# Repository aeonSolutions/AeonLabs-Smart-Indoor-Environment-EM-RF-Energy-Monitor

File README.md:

[ ](https://discord.gg/hw3j3RwfJf)

[PCB-Prototyping-Catalogue](https://github.com/aeonSolutions/PCB-Prototyping-Catalogue)  >>   [Home-Automation](https://github.com/aeonSolutions/PCB-Prototyping-Catalogue/tree/main/Home-Automation)  >>  [Safety & Health](https://github.com/aeonSolutions/AeonLabs-Safety-Health)   >>  >>  Smart Indoor Environment EM RF Energy Monitor

<br>

⚠️ **Start by reading the documentation first**. [Click here to open it](https://github.com/aeonSolutions/AeonLabs-Safety-Health/wiki) 

# Smart Indoor Environment EM RF Energy Monitor

**The Problem**

Nowadays there are a plethora of electronic devices with wireless electromagnetic (EM) capabilities. So much, is possible, for one living in a building apartment to query nearby neighboring devices. Such superposition of EM frequencies increases the risk of random (or not) energy spikes within any indoor spaces where the different devices' wireless signals exist simultaneously. The most common danger to the health of a person is found in the literature by "electromagnetic burns". Although such energy spike events are not common, when devices are setup and even programmed to broadcast in such a way are always dangerous to one's health.  

**The Idea**

This Smart Indoor Environment EM RF Energy Monitor does not solve the electromagnetic health concern one may have indoors. However, is a step forward in correctly identifying such electromagnetic disturbances nearby, for instance, when observing recurrently a mid-air energy spike, with the most common visual effect, a really small bright light flash. This smart device is able to do electromagnetic (EM) radio frequency (RF) measurements in a room and send data measurements to a local home server, alternatively to a public cloud server, for instance, to the authorities on a data repository ( see http://wwww.dataverse.org). Another important characteristic of this smart device is in the ability to deliver data to a server with a Unique Data Fingerprint Identification (UDF-ID),  which makes collected data more trustworthy of its origins.

<br>

### Status

 Not yet tested.

<br>

### Circuit Schematic 

<br>
  
### Known PCB bugs
This public revision of the PCB electronics has a few unknown errors. 

<br>

<br>
  
  ## Compatibility

<p align="center">

</p>

<br>

## What one additionally needs
- [USB to UART/USB TTL firmware burner for 5V and 3.3V MCUs ](https://github.com/aeonSolutions/PCB-Prototyping-Catalogue/blob/main/DIY-Maker/README.md) 
<br />
<br />

**Get a Notification on every PCB update**

|  | You can fill in your [email here (Google form)](https://docs.google.com/forms/d/e/1FAIpQLScErMgQYRdA-umvCjvTPPrCO7Lg1QYowTxb7vfa8cTfrcPEAA/viewform?usp=pp_url) and I'll send a reminder when a new PCB prototype is made available here or a new revision for an existing PCB. Stay tuned! |
|-------------|------|

<br />

## Buy the PRO version on Tindie

|  | To all those not into electronics and still liked and want to own any of the listed PCB for smart devices can buy the PRO version on Tindie ready to install and use. |
|-------------|------|

### Useful links 
Below is a list of links with useful information about these kinds of abusive and many times criminal and terrorist usages.
[continue reading ...](https://github.com/aeonSolutions/AeonLabs-Safety-Health/wiki/Useful-Links)

<br />
<br />

**Get a Notification on every PCB update**

|  | You can fill in your [email here (Google form)](https://docs.google.com/forms/d/e/1FAIpQLScErMgQYRdA-umvCjvTPPrCO7Lg1QYowTxb7vfa8cTfrcPEAA/viewform?usp=pp_url) and I'll send a reminder when a new PCB prototype is made available here or a new revision for an existing PCB. Stay tuned! |
|-------------|------|

<br>

**Hire AeonLabs** <br>
If you like my work here and are looking to design and deploy your own smart device find [here](https://github.com/aeonSolutions/PCB-Prototyping-Catalogue/wiki/How-to-Hire-AeonLabs) how to hire me. 

<br>

## Author

You can get in touch with me on my LinkedIn Profile:

#### Miguel Tomas

You can also follow my GitHub Profile to stay updated about my latest projects: 

<br>

### Be supportive of my dedication and work towards technology education and buy me a cup of coffee
The PCB Design Files I provide here for anyone to use are free. If you like this Smart Device or use it, please consider buying me a cup of coffee, a slice of pizza, or a book to help me study, eat, and think new PCB design files.

<br />

### Make a donation on Paypal
Make a donation on PayPal and get a TAX refund*.

### License

Before proceeding to download any of AeonLabs open source code for software solutions and/or open hardware electronics for smart devices and data acquisition make sure you are choosing the right license for your project. See [AeonLabs Solutions for Open Hardware & Open Source Code](https://github.com/aeonSolutions/PCB-Prototyping-Catalogue/wiki/AeonLabs-Solutions-for-Open-Hardware-&-Source-Development) for more information. For commercial business solutions contact AeonLabs for more information ℹ️ using the contacts above. Thank you 🙏.

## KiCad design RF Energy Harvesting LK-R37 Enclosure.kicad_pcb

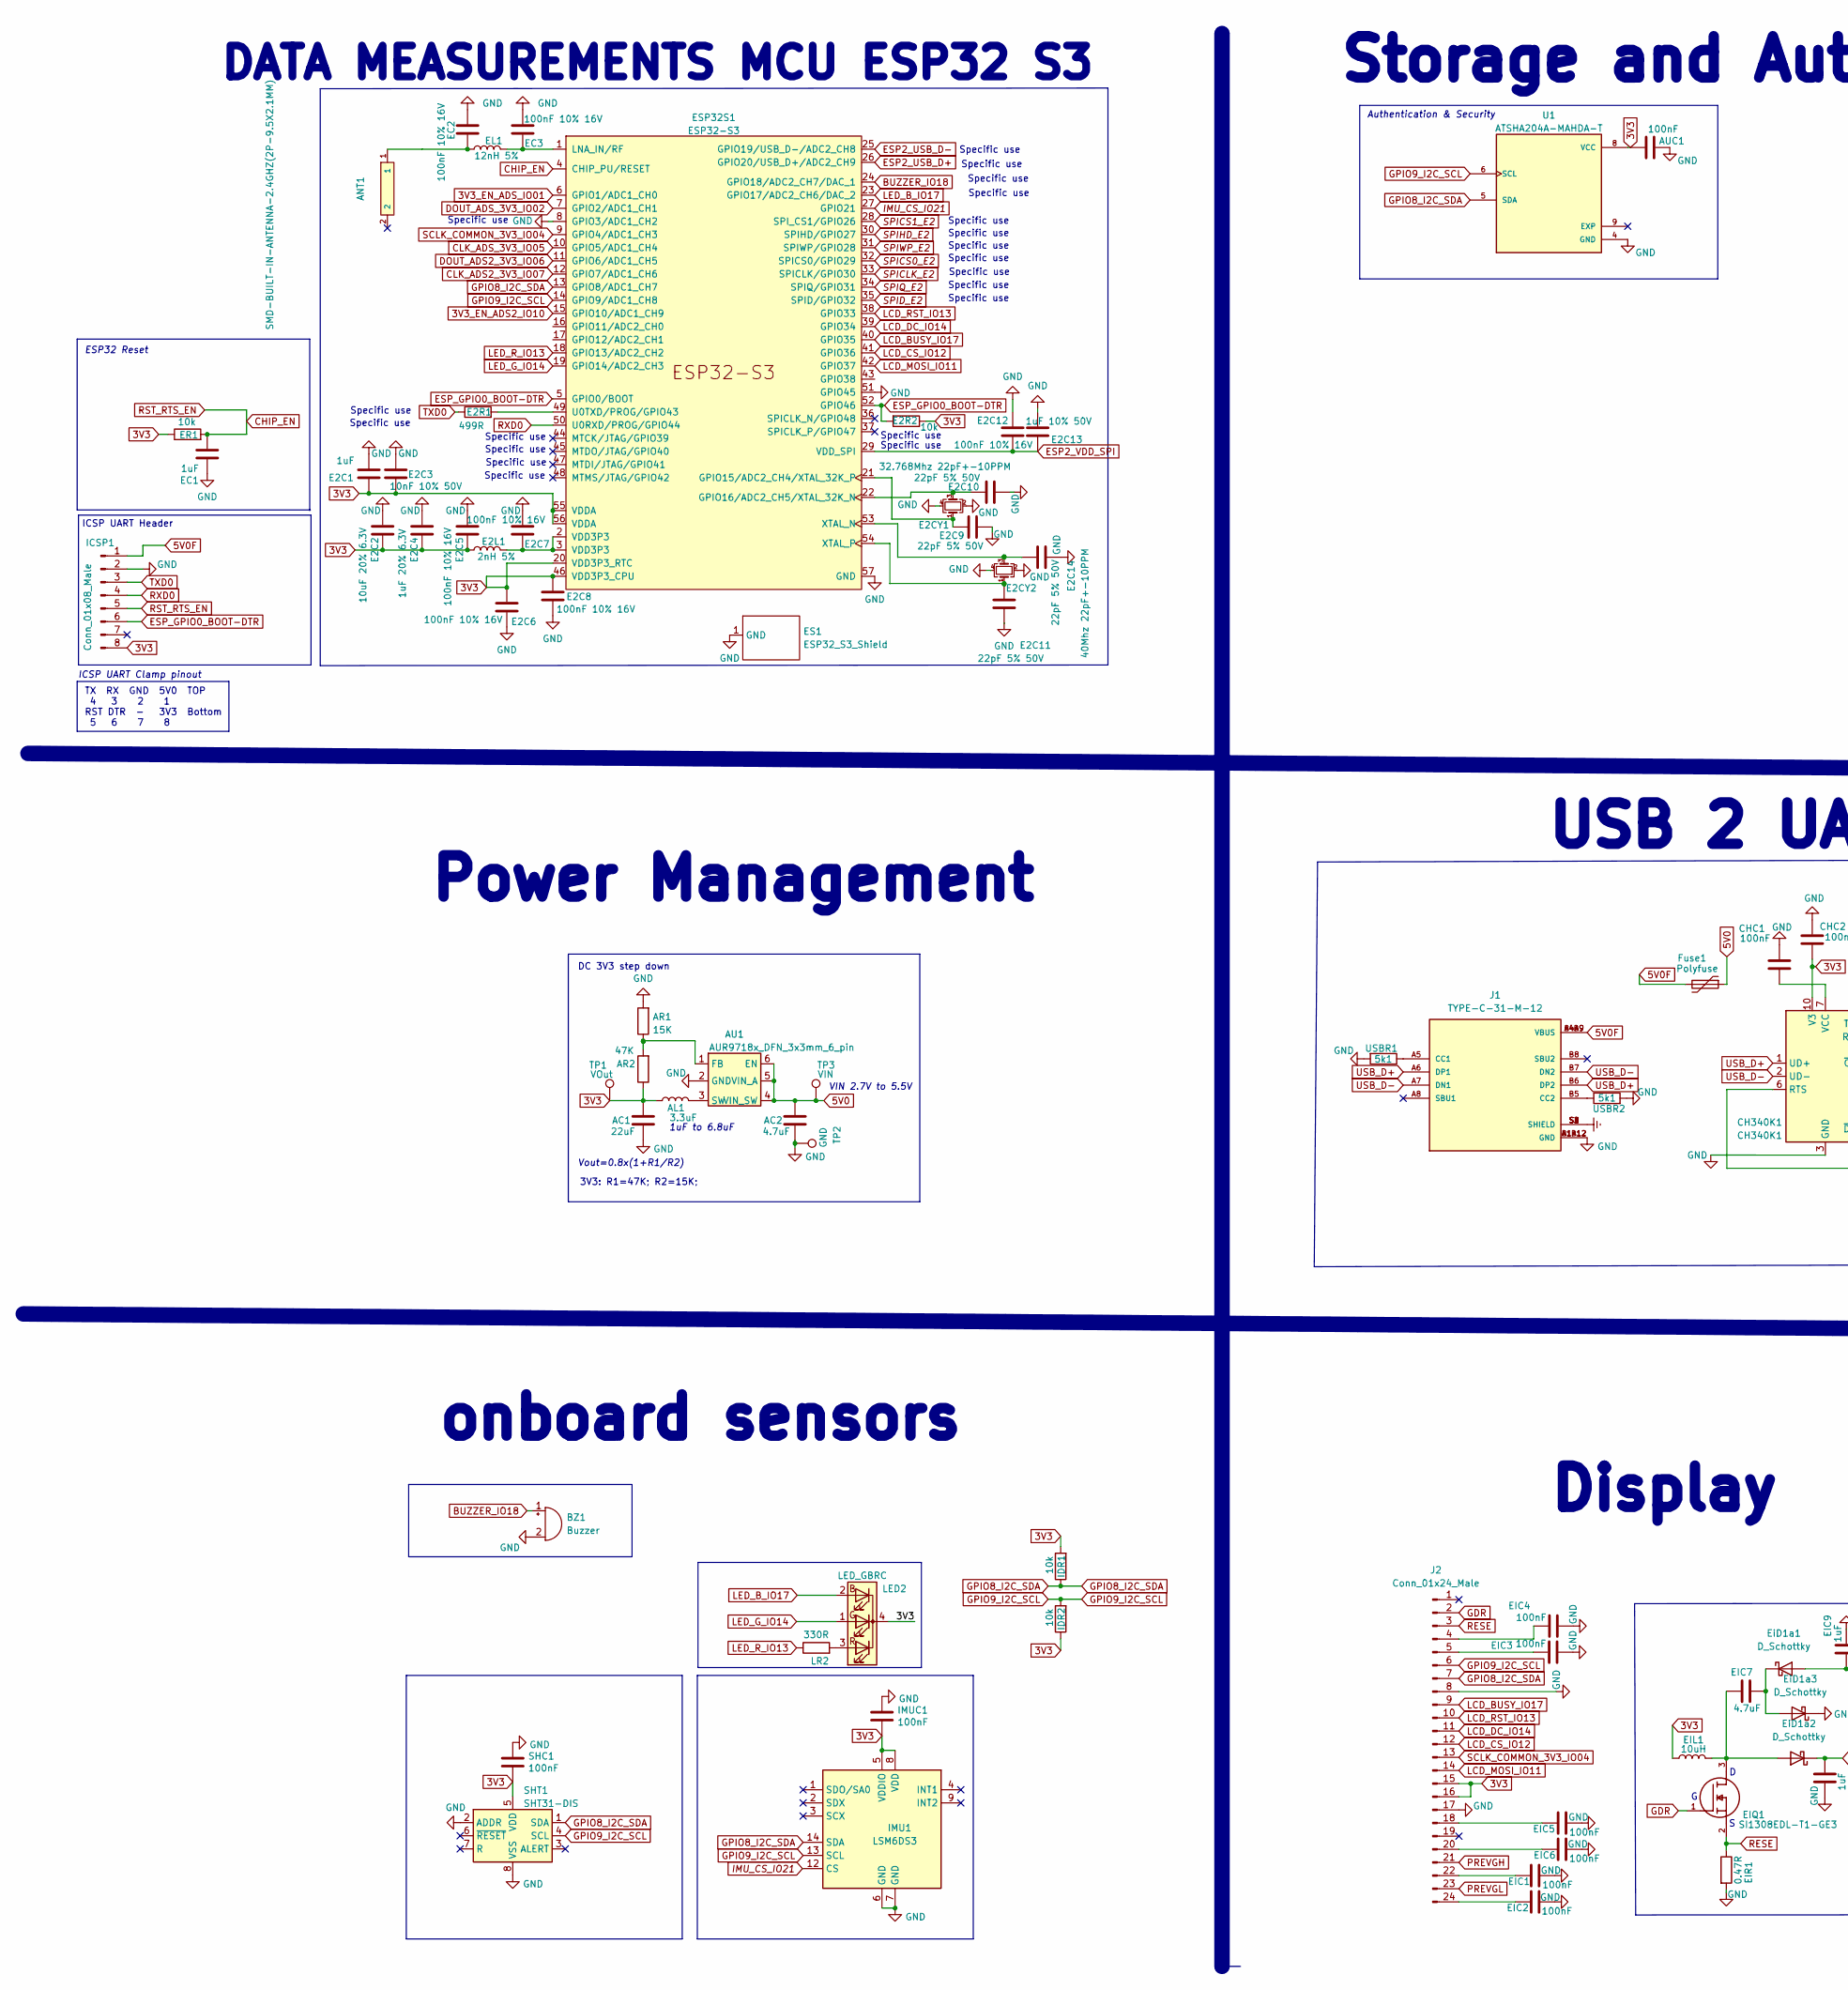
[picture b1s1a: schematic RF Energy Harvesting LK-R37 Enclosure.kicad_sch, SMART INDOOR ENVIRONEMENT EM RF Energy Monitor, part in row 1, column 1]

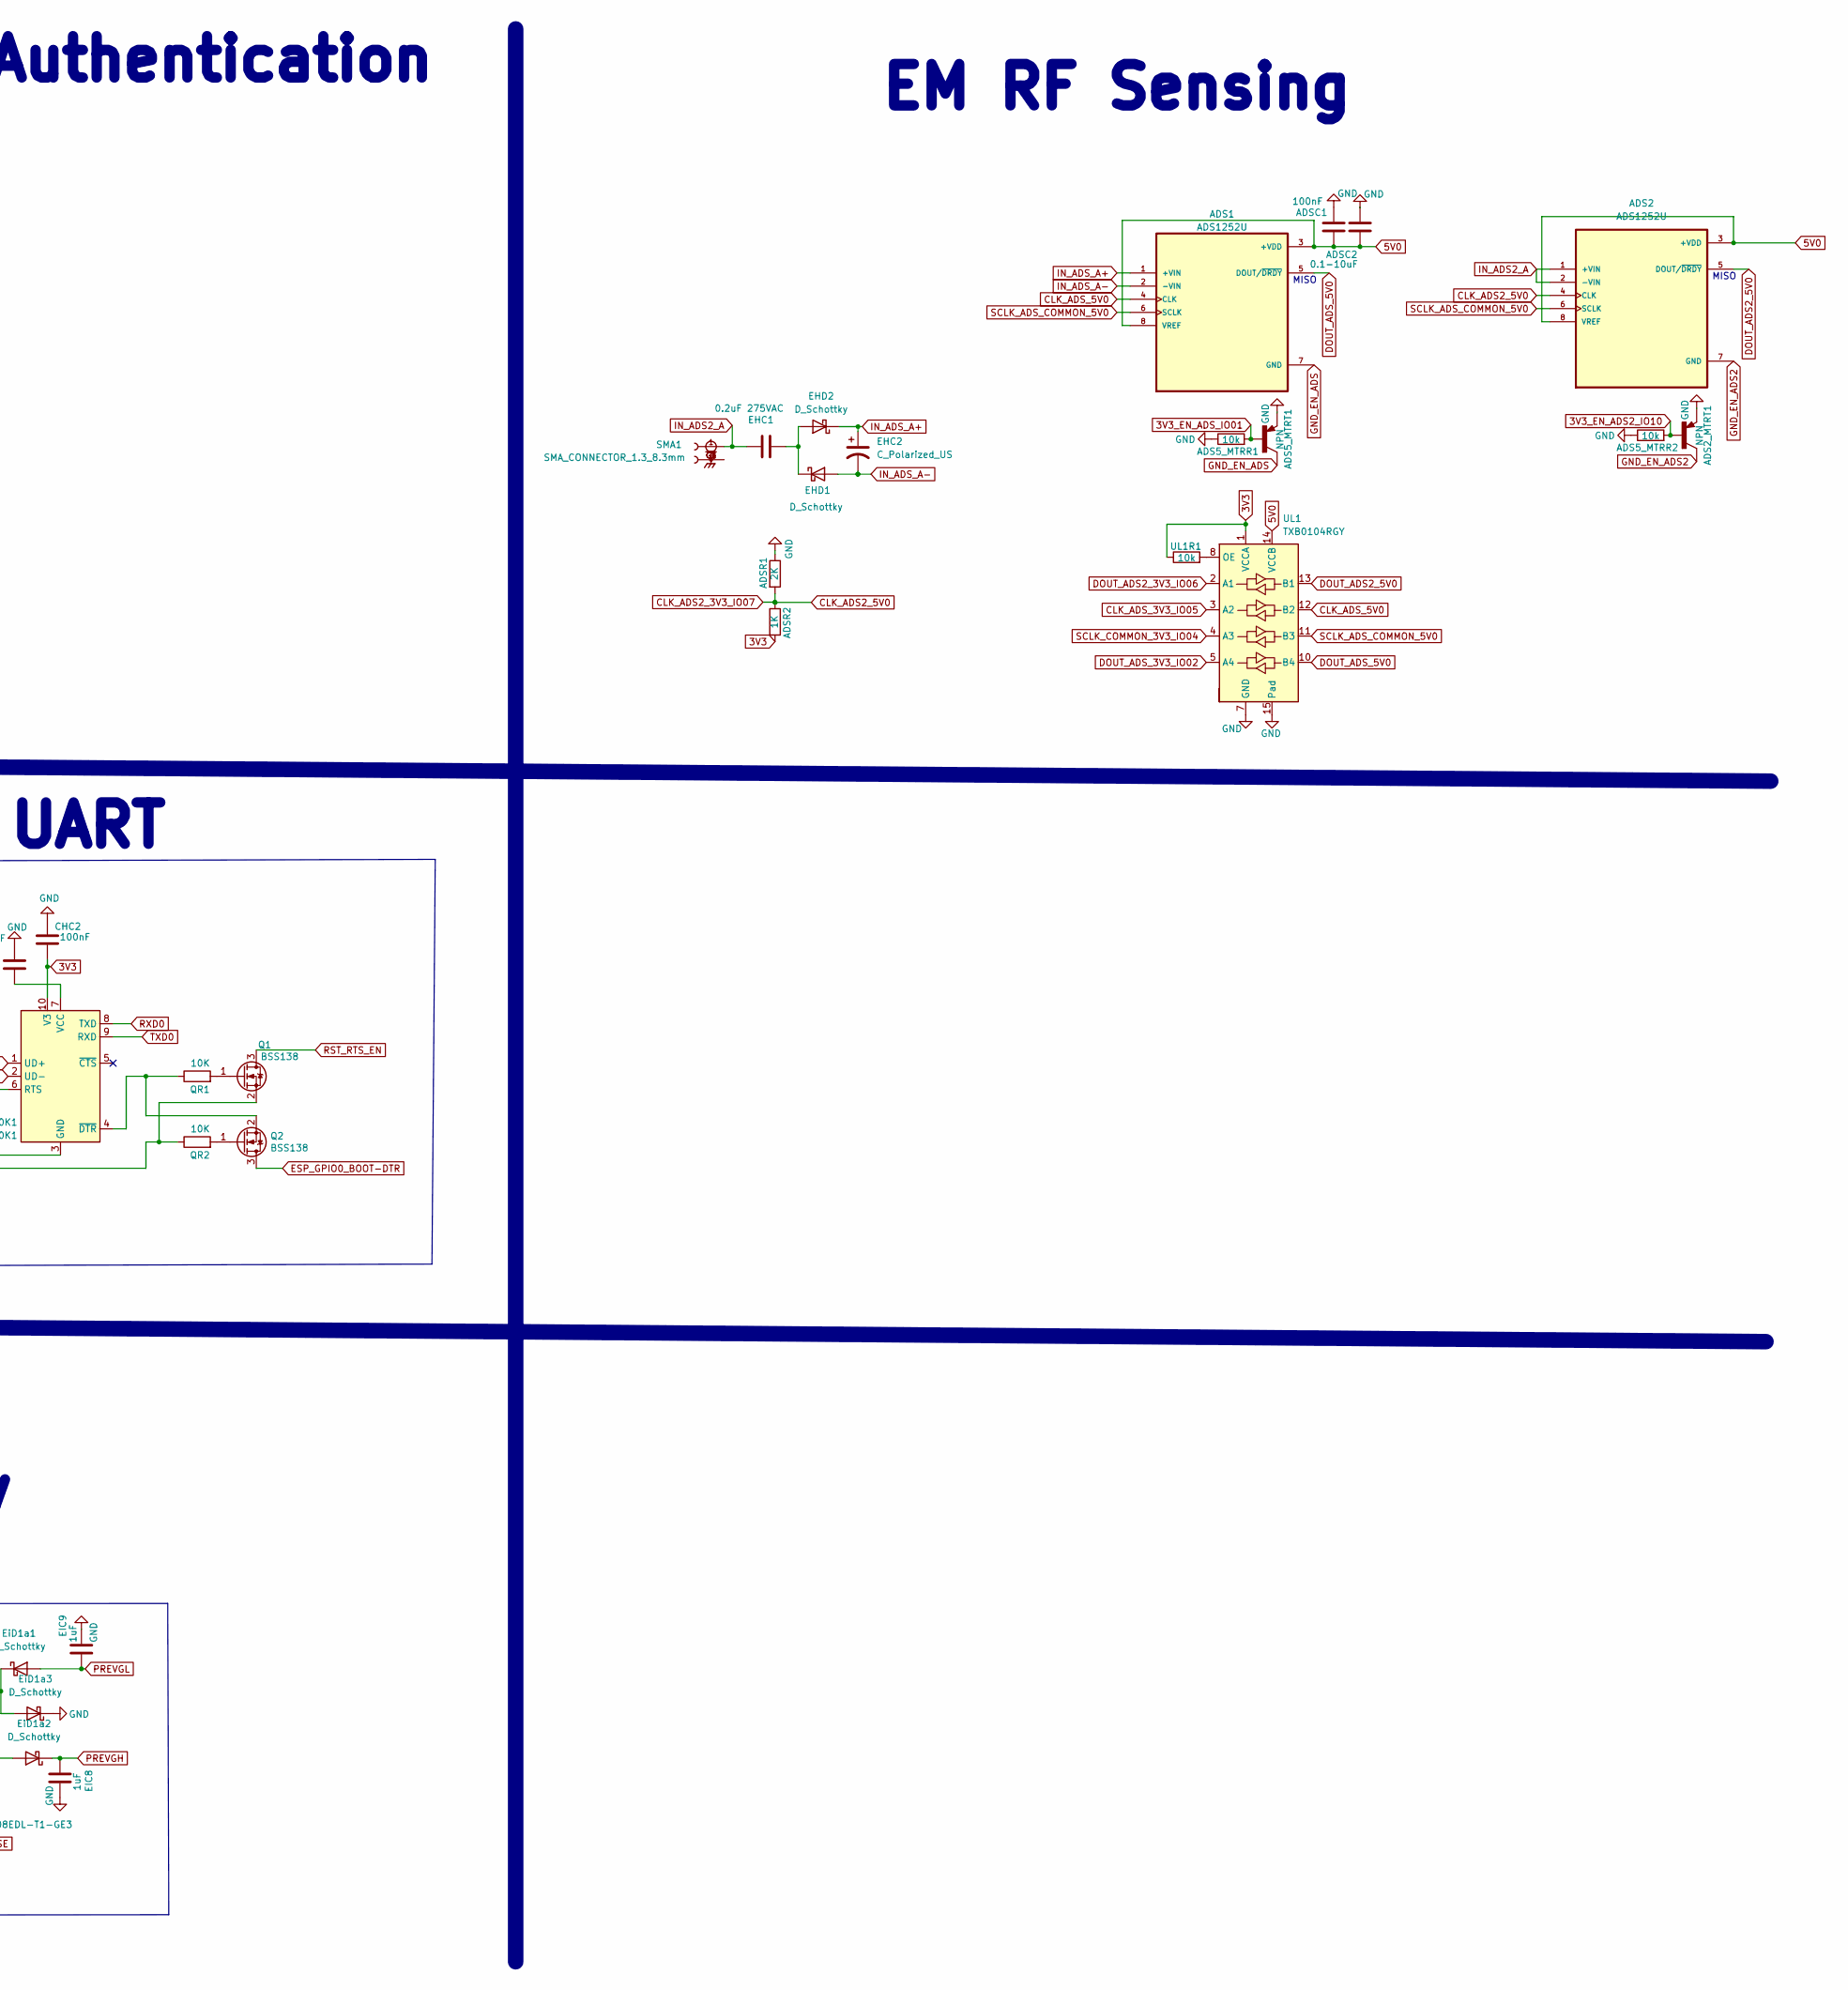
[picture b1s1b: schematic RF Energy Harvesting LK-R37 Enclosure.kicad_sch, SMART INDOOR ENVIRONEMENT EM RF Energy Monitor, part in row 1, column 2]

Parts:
AC1: 22uF; C_0805_2012Metric_Pad1.18x1.45mm_HandSolder
AC2: 4.7uF; C_0805_2012Metric_Pad1.18x1.45mm_HandSolder
ADS1, ADS2: ADS1252U; ADS1252 SOIC127P599X175-8N
ADS2_MTRT1, ADS5_MTRT1: NPN; SOT-23; PARTREV C2001
ADS5_MTRR1, ADS5_MTRR2: 10k; R_0603_1608Metric
ADSC1: 100nF; C_0603_1608Metric
ADSC2: 0.1-10uF; C_0805_2012Metric
ADSR1: 2K; R_0603_1608Metric
ADSR2: 1K; R_0603_1608Metric
AL1: 3.3uF; L_1210_3225Metric
ANT1: SMD-BUILT-IN-ANTENNA-2.4GHZ(2P-9.5X2.1MM); AN9520_ANT2-SMD-9.5X2.1X1.0MM
AR1: 15K; R_0805_2012Metric_Pad1.20x1.40mm_HandSolder
AR2: 47K; R_0805_2012Metric_Pad1.20x1.40mm_HandSolder
AU1: AUR9718x_DFN_3x3mm_6_pin; AUR9718 ST1S09 SON95P300X300X100-7N
AUC1: 100nF; C_0603_1608Metric
BZ1: Buzzer; MagneticBuzzer_Kobitone_254-EMB84Q-RO
CH340K1: CH340K1; SSOP-10_3.9x4.9mm_P1.00mm
CHC1, CHC2: 100nF; C_0603_1608Metric
E2C1: 1uF; C_0805_2012Metric
E2C2: 10uF 20% 6.3V; C_0805_2012Metric
E2C3: 10nF 10% 50V; C_0603_1608Metric
E2C4: 1uF 20% 6.3V; C_0805_2012Metric
E2C5, E2C6, E2C7, E2C8, E2C12: 100nF 10% 16V; C_0603_1608Metric
E2C9, E2C10, E2C11, E2C14: 22pF 5% 50V; C_0603_1608Metric
E2C13: 1uF 10% 50V; C_0805_2012Metric
E2CY1: 32.768Mhz 22pF+-10PPM; Crystal_SMD_EuroQuartz_MT-4Pin_3.2x2.5mm
E2CY2: 40Mhz 22pF+-10PPM; Crystal_SMD_EuroQuartz_MT-4Pin_3.2x2.5mm
E2L1: 2nH 5%; L_0805_2012Metric
E2R1: 499R; R_0603_1608Metric
E2R2: 10k; R_0603_1608Metric
EC1: 1uF; C_0603_1608Metric
EC2, EC3: 100nF 10% 16V; C_0603_1608Metric
EHC1: 0.2uF 275VAC; C_Rect_L4.0mm_W2.5mm_P2.50mm
EHC2: C_Polarized_US; C_Rect_L4.0mm_W2.5mm_P2.50mm
EHD1, EHD2: D_Schottky; D_SOD-323
EIC1, EIC2, EIC3, EIC4, EIC5, EIC6: 100nF; C_0603_1608Metric
EIC7: 4.7uF; C_0603_1608Metric
EIC8, EIC9: 1uF; C_0603_1608Metric
EIL1: 10uH; L_0805_2012Metric
EIQ1: SI1308EDL-T1-GE3; SOT-323_SC-70; Mouser_Part_Number 78-SI1308EDL-T1-GE3
EIR1: 0.47R; R_0603_1608Metric
EL1: 12nH 5%; L_0805_2012Metric
ER1: 10k; R_0603_1608Metric
ES1: ESP32_S3_Shield; ESP32-S3 GND Shield
ESP32S1: ESP32-S3; QFN-56-1EP_7x7mm_P0.4mm_EP5.6x5.6mm
EiD1a1, EiD1a2, EiD1a3: D_Schottky; D_SOD-323
Fuse1: Polyfuse; Fuse_1206_3216Metric
ICSP1: Conn_01x08_Male; SOIC_clipProgSmall
IDR1, IDR2: 10k; R_0603_1608Metric
IMU1: LSM6DS3; LSM6DS3 PQFN50P300X250X86-14N
IMUC1: 100nF; C_0603_1608Metric
J1: TYPE-C-31-M-12; USB C HRO_TYPE-C-31-M-12; PARTREV A
J2: Conn_01x24_Male; FFC 24pin 0.5 pitch vertical GCT_FFC2A32-24-T
LED2: LED_GBRC; LED_1206_3210_RGB_Metric
LR2: 330R; R_0603_1608Metric
Q1, Q2: BSS138; SOT-23
QR1, QR2: 10K; R_0603_1608Metric
SHC1: 100nF; C_0603_1608Metric
SHT1: SHT31-DIS; SHT3x SON50P250X250X100-9N-D
SMA1: SMA_CONNECTOR_1.3_8.3mm; MMCX_Molex_73415-1471_Vertical; PARTREV 1.3
TP1: VOut; TestPoint_Pad_D1.0mm
TP2: GND; TestPoint_Pad_D1.0mm
TP3: VIN; TestPoint_Pad_D1.0mm
U1: ATSHA204A-MAHDA-T; ATSHA204A Auth SOIC8; PART_REV A
UL1: TXB0104RGY; Texas_S-PVQFN-N14
UL1R1: 10k; R_0603_1608Metric
USBR1, USBR2: 5k1; R_0603_1608Metric

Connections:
3V3: AC1.1, ADSR2.2, AL1.1, AR2.1, AUC1.2, CH340K1.10 (V3), CHC2.1, E2C1.2, E2C2.1, E2C3.2, E2C4.1, E2C5.1, E2C6.1, E2C8.1, E2L1.1, E2R2.1, EIL1.1, ER1.1, ESP32S1.20 (VDD3P3_RTC), ESP32S1.46 (VDD3P3_CPU), ESP32S1.55 (VDDA), ESP32S1.56 (VDDA), ICSP1.8, IDR1.2, IDR2.1, IMU1.5 (VDDIO), IMU1.8 (VDD), IMUC1.2, J2.15, J2.16, LED2.4 (K), SHC1.2, SHT1.5 (VDD), TP1.1, U1.8 (VCC), UL1.1 (VCCA), UL1R1.1
3V3_EN_ADS2_IO10: ADS2_MTRT1.1, ADS5_MTRR2.2, ESP32S1.15 (GPIO10/ADC1_CH9)
3V3_EN_ADS_IO01: ADS5_MTRR1.2, ADS5_MTRT1.1, ESP32S1.6 (GPIO1/ADC1_CH0)
5V0: AC2.1, ADS1.3 (+VDD), ADS1.8 (VREF), ADS2.3 (+VDD), ADS2.8 (VREF), ADSC1.1, ADSC2.1, AU1.4 (VIN_SW), AU1.5 (VIN_A), AU1.6 (EN), Fuse1.1, TP3.1, UL1.14 (VCCB)
5V0F: Fuse1.2, ICSP1.1, J1.A4B9 (VBUS), J1.B4A9 (VBUS)
BUZZER_IO18: BZ1.1 (-), ESP32S1.24 (GPIO18/ADC2_CH7/DAC_1)
CHIP_EN: EC1.2, ER1.2, ESP32S1.4 (CHIP_PU/RESET), ICSP1.5, Q1.3 (D)
CLK_ADS2_3V3_IO07: ADS2.4 (CLK), ADSR1.2, ADSR2.1, ESP32S1.12 (GPIO7/ADC1_CH6)
CLK_ADS_3V3_IO05: ESP32S1.10 (GPIO5/ADC1_CH4), UL1.3 (A2)
CLK_ADS_5V0: ADS1.4 (CLK), UL1.12 (B2)
DOUT_ADS2_3V3_IO06: ESP32S1.11 (GPIO6/ADC1_CH5), UL1.2 (A1)
DOUT_ADS2_5V0: ADS2.5 (DOUT/~DRDY), UL1.13 (B1)
DOUT_ADS_3V3_IO02: ESP32S1.7 (GPIO2/ADC1_CH1), UL1.5 (A4)
DOUT_ADS_5V0: ADS1.5 (DOUT/~DRDY), UL1.10 (B4)
ESP2_USB_D+: ESP32S1.26 (GPIO20/USB_D+/ADC2_CH9)
ESP2_USB_D-: ESP32S1.25 (GPIO19/USB_D-/ADC2_CH8)
ESP2_VDD_SPI: E2C12.1, E2C13.1, ESP32S1.29 (VDD_SPI)
ESP_GPIO0_BOOT-DTR: E2R2.2, ESP32S1.5 (GPIO0/BOOT), ESP32S1.52 (GPIO46), ICSP1.6, Q2.3 (D)
Earth: J1.S1 (SHIELD), J1.S2 (SHIELD), J1.S3 (SHIELD), J1.S4 (SHIELD)
GDR: EIQ1.1, J2.2
GND: AC1.2, AC2.2, ADS2_MTRT1.2, ADS5_MTRR1.1, ADS5_MTRR2.1, ADS5_MTRT1.2, ADSC1.2, ADSC2.2, ADSR1.1, AR1.2, AU1.2 (GND), AUC1.1, BZ1.2 (+), CH340K1.3 (GND), CHC1.2, CHC2.2, E2C1.1, E2C2.2, E2C3.1, E2C4.2, E2C5.2, E2C6.2, E2C7.2, E2C8.2, E2C9.2, E2C10.2, E2C11.2, E2C12.2, E2C13.2, E2C14.2, E2CY1.2, E2CY1.4, E2CY2.2, E2CY2.4, EC1.1, EC2.2, EC3.2, EIC1.2, EIC2.2, EIC3.2, EIC4.2, EIC5.2, EIC6.2, EIC8.2, EIC9.2, EIR1.2, ES1.1 (GND), ESP32S1.8 (GPIO3/ADC1_CH2), ESP32S1.51 (GPIO45), ESP32S1.57 (GND), EiD1a3.1 (K), ICSP1.2, IMU1.6 (GND), IMU1.7 (GND), IMUC1.1, J1.A1B12 (GND), J1.B1A12 (GND), J2.8, J2.17, SHC1.1, SHT1.2 (ADDR), SHT1.8 (VSS), SHT1.9 (VSS), TP2.1, U1.4 (GND), UL1.7 (GND), UL1.15 (Pad), USBR1.2, USBR2.2
GND_EN_ADS: ADS1.7 (GND), ADS5_MTRT1.3
GND_EN_ADS2: ADS2.7 (GND), ADS2_MTRT1.3
GPIO8_I2C_SDA: ESP32S1.13 (GPIO8/ADC1_CH7), IDR1.1, IMU1.14 (SDA), J2.7, SHT1.1 (SDA), U1.5 (SDA)
GPIO9_I2C_SCL: ESP32S1.14 (GPIO9/ADC1_CH8), IDR2.2, IMU1.13 (SCL), J2.6, SHT1.4 (SCL), U1.6 (SCL)
IMU_CS_IO21: ESP32S1.27 (GPIO21), IMU1.12 (CS)
IN_ADS2_A: ADS2.1 (+VIN), ADS2.2 (-VIN), EHC1.2, SMA1.1
IN_ADS_A+: ADS1.1 (+VIN), EHC2.1, EHD2.1 (K)
IN_ADS_A-: ADS1.2 (-VIN), EHC2.2, EHD1.2 (A)
LCD_BUSY_IO17: ESP32S1.40 (GPIO35), J2.9
LCD_CS_IO12: ESP32S1.41 (GPIO36), J2.12
LCD_DC_IO14: ESP32S1.39 (GPIO34), J2.11
LCD_MOSI_IO11: ESP32S1.42 (GPIO37), J2.14
LCD_RST_IO13: ESP32S1.38 (GPIO33), J2.10
LED_B_IO17: ESP32S1.23 (GPIO17/ADC2_CH6/DAC_2), LED2.2 (BA)
LED_G_IO14: ESP32S1.19 (GPIO14/ADC2_CH3), LED2.1 (GA)
LED_R_IO13: ESP32S1.18 (GPIO13/ADC2_CH2), LR2.1
unnamed: AL1.2, AU1.3 (SW)
unnamed: ANT1.1, EC2.1, EL1.1
unnamed: AR1.1, AR2.2, AU1.1 (FB)
unnamed: CH340K1.4 (~DTR), Q2.2 (S), QR1.1
unnamed: CH340K1.6 (RTS), Q1.2 (S), QR2.1
unnamed: CH340K1.7 (VCC), CHC1.1
unnamed: E2C7.1, E2L1.2, ESP32S1.2 (VDD3P3), ESP32S1.3 (VDD3P3)
unnamed: E2C9.1, E2CY1.1, ESP32S1.21 (GPIO15/ADC2_CH4/XTAL_32K_P)
unnamed: E2C10.1, E2CY1.3, ESP32S1.22 (GPIO16/ADC2_CH5/XTAL_32K_N)
unnamed: E2C11.1, E2CY2.1, ESP32S1.54 (XTAL_P)
unnamed: E2C14.1, E2CY2.3, ESP32S1.53 (XTAL_N)
unnamed: E2R1.2, ESP32S1.49 (U0TXD/PROG/GPIO43)
unnamed: EC3.1, EL1.2, ESP32S1.1 (LNA_IN/RF)
unnamed: EHC1.1, EHD1.1 (K), EHD2.2 (A)
unnamed: EIC1.1, J2.22
unnamed: EIC2.1, J2.24
unnamed: EIC3.1, J2.5
unnamed: EIC4.1, J2.4
unnamed: EIC5.1, J2.18
unnamed: EIC6.1, J2.20
unnamed: EIC7.1, EiD1a1.1 (K), EiD1a3.2 (A)
unnamed: EIC7.2, EIL1.2, EIQ1.3, EiD1a2.2 (A)
unnamed: J1.A5 (CC1), USBR1.1
unnamed: J1.B5 (CC2), USBR2.1
unnamed: LED2.3 (RA), LR2.2
unnamed: Q1.1 (G), QR1.2
unnamed: Q2.1 (G), QR2.2
unnamed: UL1.8 (OE), UL1R1.2
PREVGH: EIC8.1, EiD1a2.1 (K), J2.21
PREVGL: EIC9.1, EiD1a1.2 (A), J2.23
RESE: EIQ1.2, EIR1.1, J2.3
RXD0: CH340K1.8 (TXD), ESP32S1.50 (U0RXD/PROG/GPIO44), ICSP1.4
SCLK_ADS_COMMON_5V0: ADS1.6 (SCLK), ADS2.6 (SCLK), UL1.11 (B3)
SCLK_COMMON_3V3_IO04: ESP32S1.9 (GPIO4/ADC1_CH3), J2.13, UL1.4 (A3)
SPICLK_E2: ESP32S1.33 (SPICLK/GPIO30)
SPICS0_E2: ESP32S1.32 (SPICS0/GPIO29)
SPICS1_E2: ESP32S1.28 (SPI_CS1/GPIO26)
SPID_E2: ESP32S1.35 (SPID/GPIO32)
SPIHD_E2: ESP32S1.30 (SPIHD/GPIO27)
SPIQ_E2: ESP32S1.34 (SPIQ/GPIO31)
SPIWP_E2: ESP32S1.31 (SPIWP/GPIO28)
TXD0: CH340K1.9 (RXD), E2R1.1, ICSP1.3
USB_D+: CH340K1.1 (UD+), J1.A6 (DP1), J1.B6 (DP2)
USB_D-: CH340K1.2 (UD-), J1.A7 (DN1), J1.B7 (DN2)

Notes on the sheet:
Authentication & Security
MISO
ICSP UART Clamp pinout
onboard sensors
Display
Specific use
3V3: R1=47K; R2=15K;
ICSP UART Header
Power Management
DATA MEASUREMENTS MCU ESP32 S3
Vout=0.8x(1+R1/R2)
USB 2 UART
VIN 2.7V to 5.5V
DC 3V3 step down
1uF to 6.8uF
ESP32 Reset
TX RX GND 5V0 TOP 4 3 2 1 RST DTR - 3V3 Bottom 5 6 7 8
EM RF Sensing
Storage and Authentication

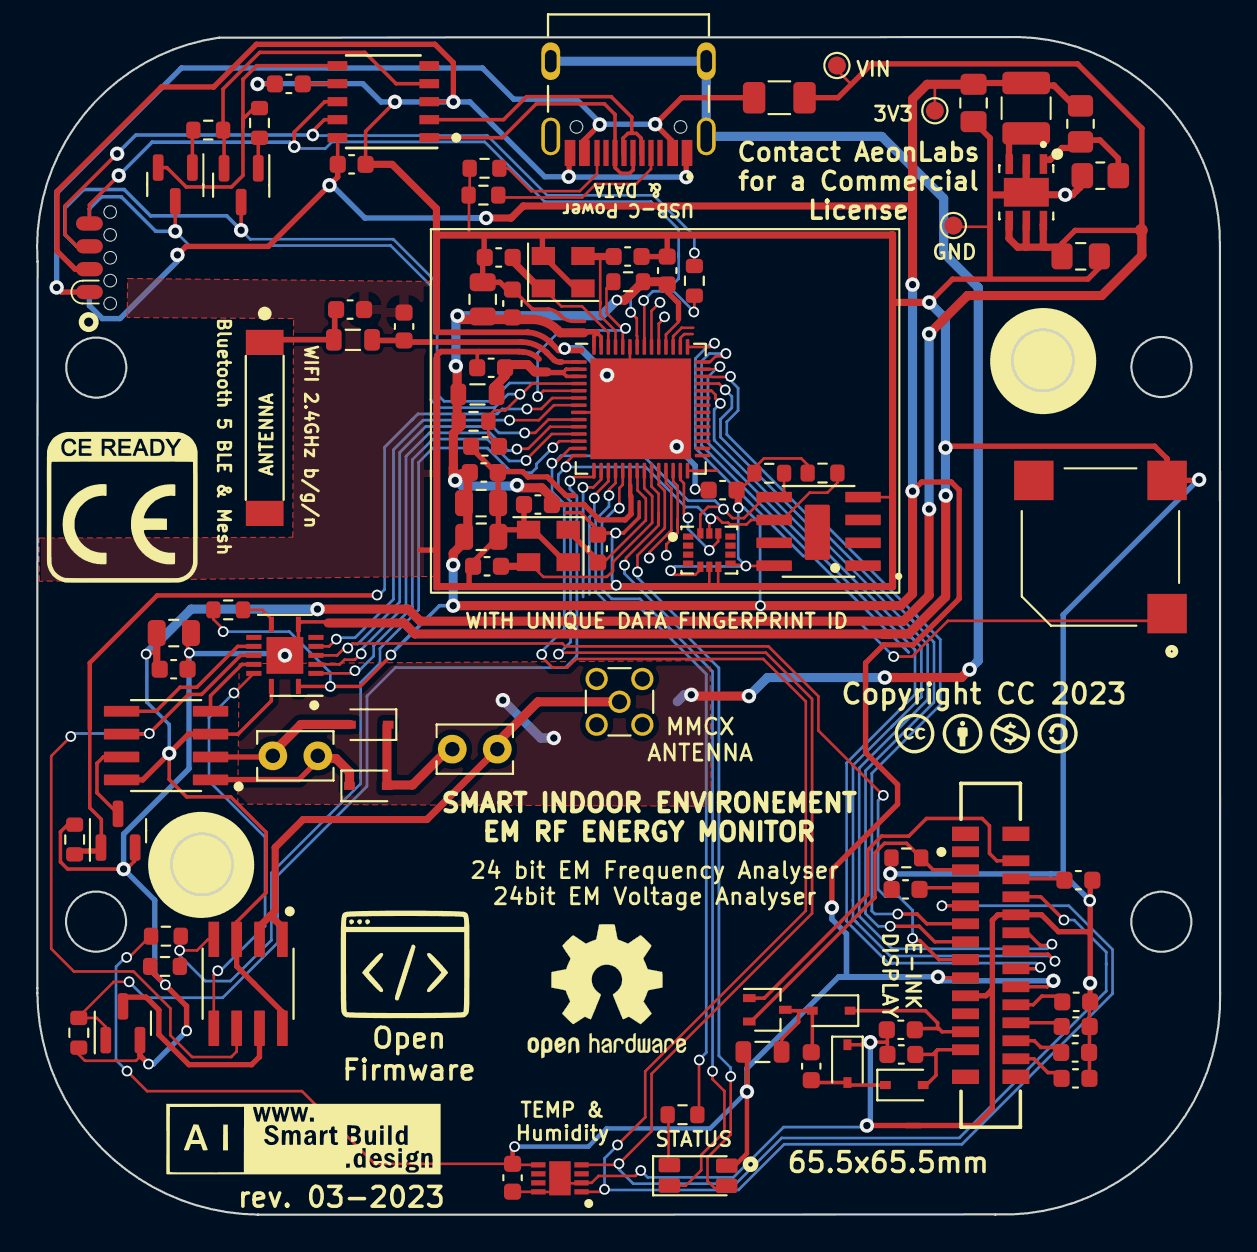
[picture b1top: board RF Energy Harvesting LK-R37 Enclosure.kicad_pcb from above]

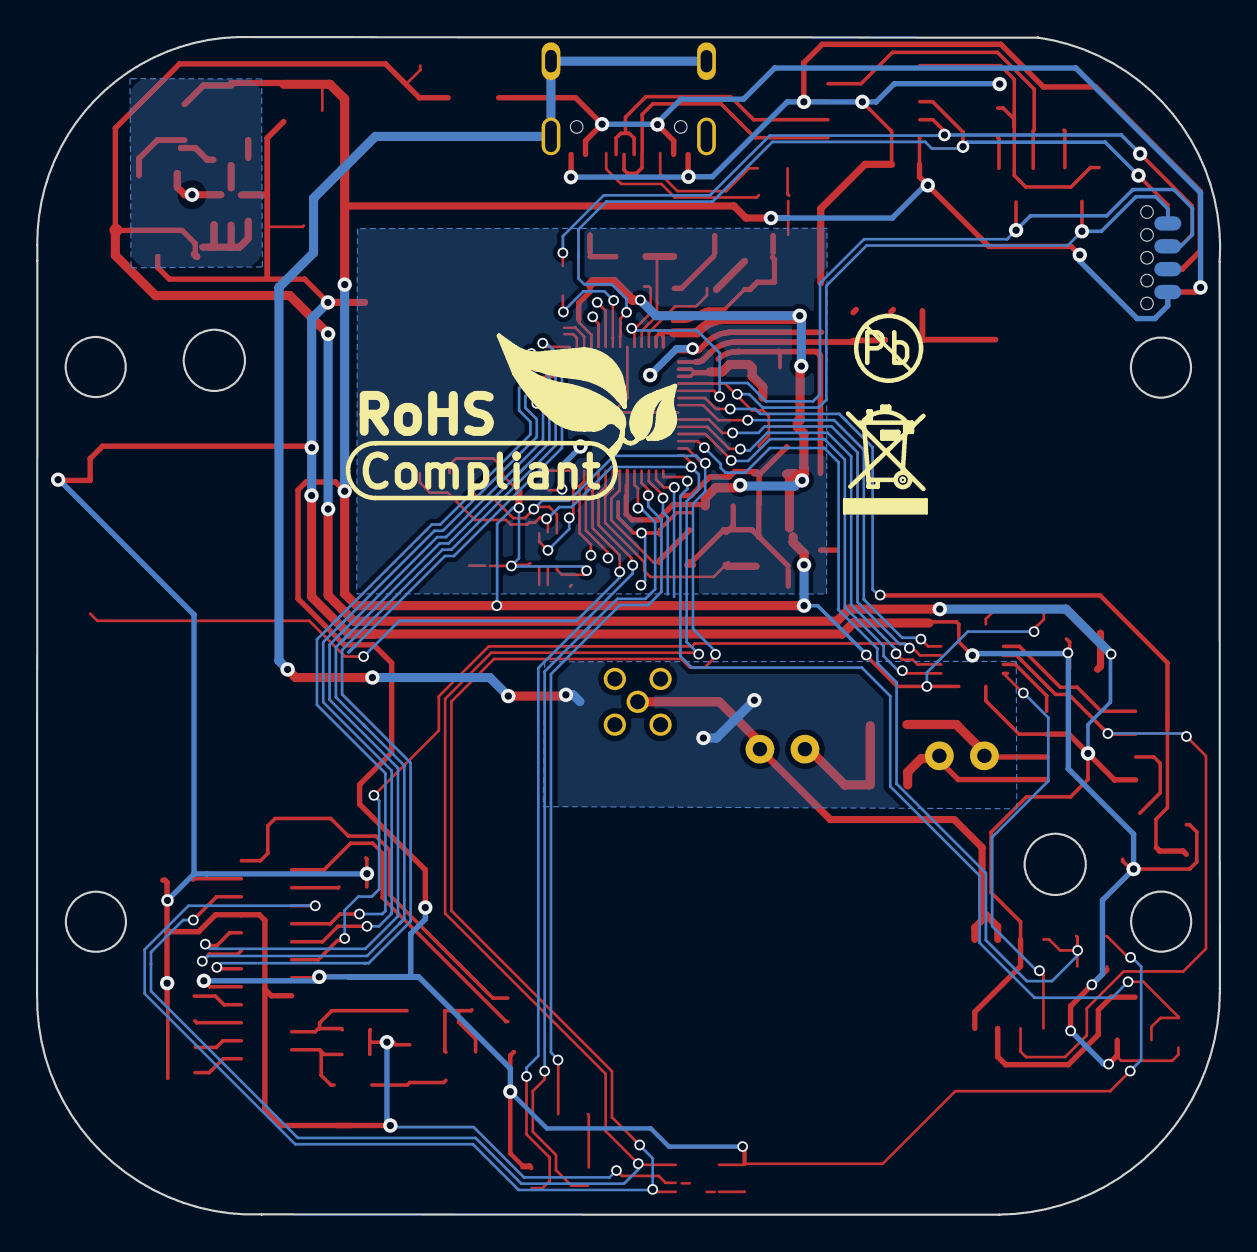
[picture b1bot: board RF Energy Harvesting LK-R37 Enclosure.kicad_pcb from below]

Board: 2 copper layers, 65.7 x 65.4 mm, 92 parts (3 on the bottom side), 71 nets.

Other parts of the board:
Sign-PbFree: LOGO_PBFREE
Sign-RecycleBin: LOGO_RECYCLEBIN_1
Sign-RoHS: LOGO_ROHS_1

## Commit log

2023-02-11 initial commit
    beta R4

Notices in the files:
RF Energy Harvesting LK-R37 Enclosure.kicad_pcb:
Copyright CC 2023
